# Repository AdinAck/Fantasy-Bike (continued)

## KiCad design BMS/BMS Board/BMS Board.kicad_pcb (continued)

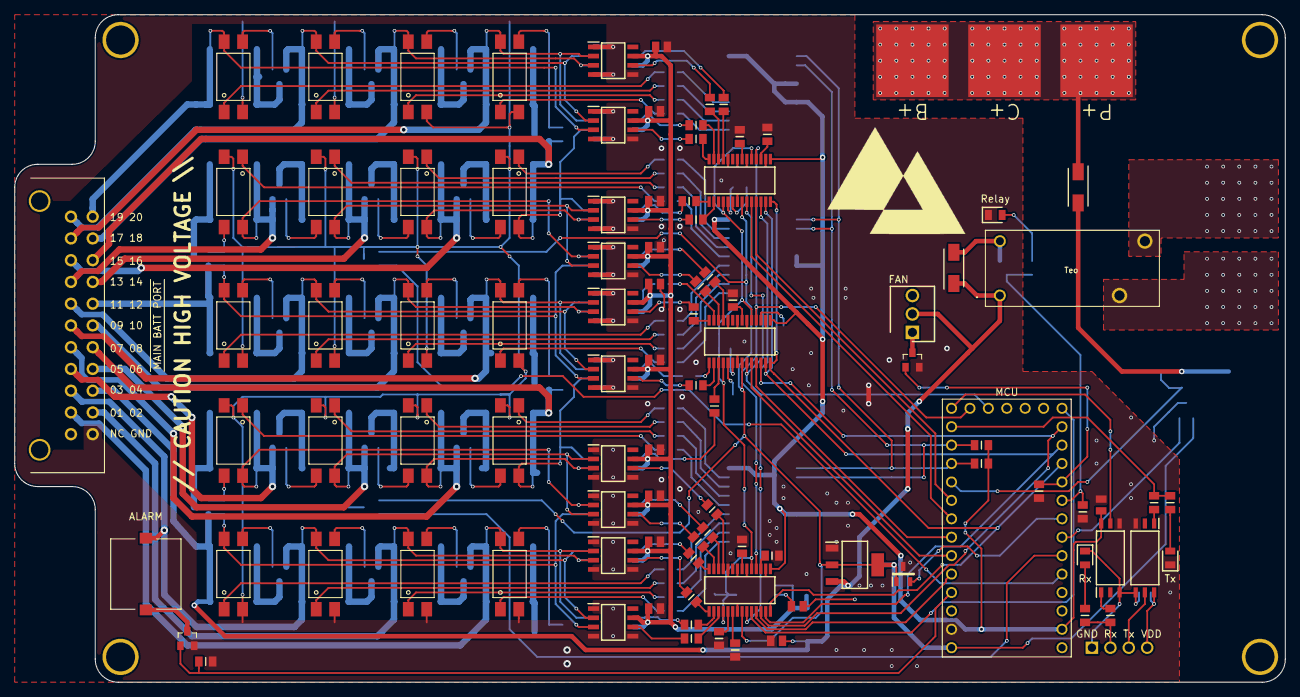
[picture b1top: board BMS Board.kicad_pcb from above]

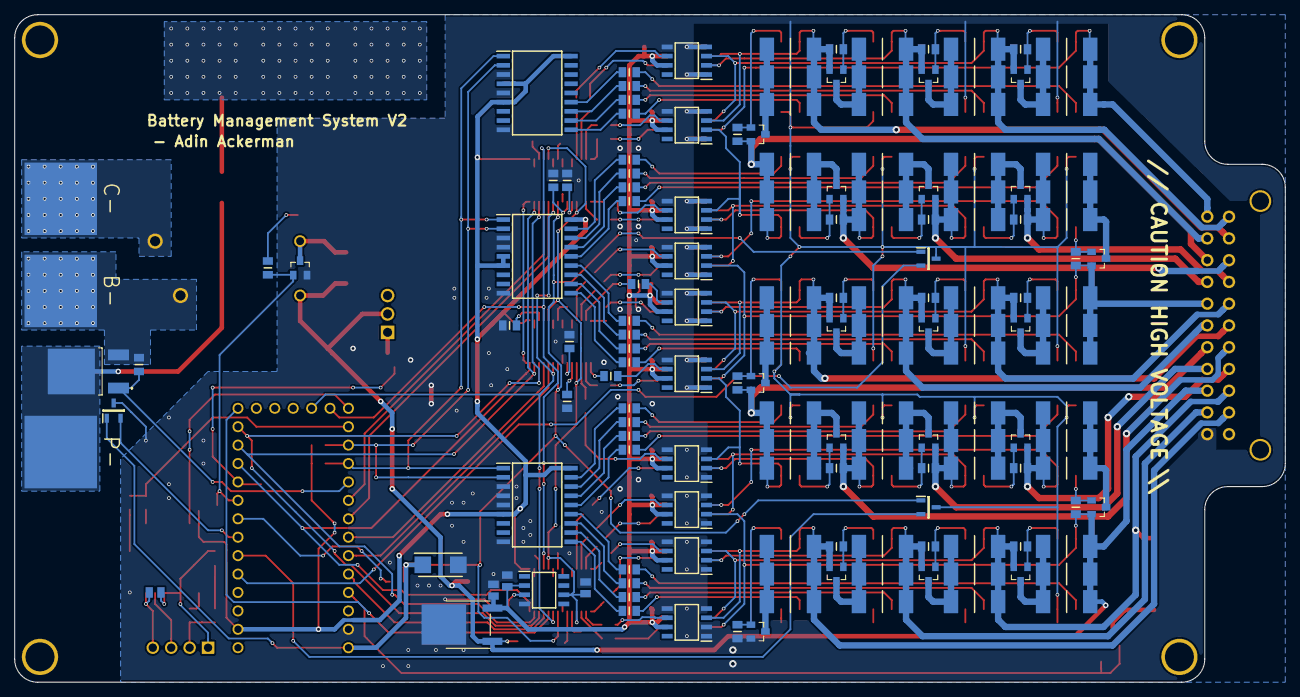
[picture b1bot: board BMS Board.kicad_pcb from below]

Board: 2 copper layers, 175.3 x 92.1 mm, 261 parts (157 on the bottom side), 197 nets.

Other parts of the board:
C18: 0805ZC104MAT2A; CAPC2012X94N
IC1, IC2: TLP2766A_TP,E; SOT127P1000X230-6N

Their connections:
/Communication/RX: IC2.5; also elsewhere on the board
unnamed 68: IC1.6; also elsewhere on the board
unnamed 69: IC1.4, IC2.3; also elsewhere on the board
unnamed 72: IC1.1; also elsewhere on the board
unnamed 74: IC1.5; also elsewhere on the board
unnamed 75: IC2.1; also elsewhere on the board

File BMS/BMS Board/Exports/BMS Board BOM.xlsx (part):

Reference | Value | Footprint | Datasheet | Capacitance | Color | Description | Height | Manufacturer_Name | Manufacturer_Part_Number | Mouser Part Number | Mouser Price/Stock | Resistance | Voltage, Current | Quantity
C1 | 08053C334KAT2A | CAPC2012X140N | https://componentsearchengine.com/Datasheets/1/08053C334KAT2A.pdf | .33 uF |  | AVX 0805 Standard 0.33uF Ceramic Multilayer Capacitor, 25 V dc, +125 | 1.4 | AVX | 08053C334KAT2A | 581-08053C334KAT2A | https://www.mouser.com/Search/Refine.aspx?Keyword=581-08053C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 |  |  | 1.0
> C2, C4-C13, C17, C18 | 0805ZC104MAT2A | CAPC2012X94N | https://componentsearchengine.com/Datasheets/1/0805ZC104MAT2A.pdf | 100nF |  | Capacitor 0805 0.1UF +/-20% 10V |  | AVX | 0805ZC104MAT2A | 581-0805ZC104MAT2A | https://www.mouser.com/Search/Refine.aspx?Keyword=581-0805ZC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 |  |  | 13.0
C3 | TPSC107K010R0150 | CAPPM6032X280N | https://componentsearchengine.com/Datasheets/1/TPSC107K010R0150.pdf | 100 uF |  | Cap Tant Solid 100uF 10V C CASE 10% (6 X 3.2 X 2.6mm) SMD 6032-28 0.15 Ohm 125C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 | 2.8 | AVX | TPSC107K010R0150 | 581-TPSC107K010R0150 | https://www.mouser.com/Search/Refine.aspx?Keyword=581-TPSC10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 |  |  | 1.0
> C14-C16 | 08053C225K4T2A | CAPC2012X94N |  | 2.2 uF |  | AVX - 08053C225K4T2A - SMD Multilayer Ceramic Capacitor, 2.2 uF, 25 V, 0805 [20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 | 0.94 | AVX | 08053C225K4T2A |  |  |  |  | 3.0
> D1, D2 | S1G | DIOM5227X250N | https://www.onsemi.com/pub/Collateral/S1M-D.pdf |  |  | ON Semi 400V 1A, Diode, 2-Pin DO-214AC S1G | 2.5 | ON Semiconductor | S1G | 512-S1G | https://www.mouser.co.uk/ProductDetail/ON-Semiconductor-Fair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 |  |  | 2.0
> H1-H4 | MountingHole | MountingHole:MountingHole_4mm_Pad_Better | ~ |  |  |  |  |  |  |  |  |  |  | 4.0
> IC1, IC2 | TLP2766A_TP,E | SOT127P1000X230-6N | https://componentsearchengine.com/Datasheets/1/TLP2766A(TP,E.pdf |  |  | High Speed Optocouplers High speed Logic output coupler; SO6L; RoHS; T&R | 2.3 | Toshiba | TLP2766A(TP,E | 757-TLP2766ATPE | https://www.mouser.co.uk/ProductDetail/Toshiba/TLP2766ATPE?q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 |  |  | 2.0
J1 | 10129379-904002BLF | HDRRA4W67P0X254_1X4_1016X254X241P | https://cdn.amphenol-icc.com/media/wysiwyg/files/drawing/101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 |  |  | Headers & Wire Housings ECONOSTIK HEADER SR RA TH 1X4 | 2.41 | Amphenol | 10129379-904002BLF | 649-1012937990402BLF | https://www.mouser.co.uk/ProductDetail/Amphenol-FCI/10129379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 |  |  | 1.0
J2 | 640456-3 | HDRV3W107P0X254_1X3_762X572X1080P | http://www.te.com/commerce/DocumentDelivery/DDEController?Ac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 |  |  | 3 way MTA straight friction lock header | 10.795 | TE Connectivity | 640456-3 | 571-6404563 | https://www.mouser.co.uk/ProductDetail/TE-Connectivity-AMP/6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 |  |  | 1.0
K1 | G5PZ-1A_DC12 | G5PZ1ADC12 | https://www.mouser.dk/datasheet/2/307/Omron_(ENG)G5PZ_E-1843616.pdf |  |  | General Purpose Relays PCB Power Relay Compact 20A, 12 VDC | 25.0 | Omron Electronics | G5PZ-1A DC12 | 653-G5PZ-1ADC12 | https://www.mouser.co.uk/ProductDetail/Omron-Electronics/G5P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 |  |  | 1.0
> LED1, LED2 | HSML-C170-T0000 | LEDC2012X90N | https://docs.broadcom.com/docs/HSML-C170-T0000-DS100 |  | Orange | CHIP,TOP MT,ALINGAP,ORG - Bulk | 0.9 | Avago Technologies | HSML-C170-T0000 | 630-HSML-C170-T0000 | https://www.mouser.co.uk/ProductDetail/Broadcom-Avago/HSML-C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 |  |  | 2.0
LED3 | HSMG-C170 | LEDC2012X80N |  |  |  | Green LED, 15 mcd 170 , 2-pin 0805 SMD Package | 0.8 | Avago Technologies | HSMG-C170 | 630-HSMG-C170 | https://www.mouser.co.uk/ProductDetail/Broadcom-Avago/HSMG-C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 |  |  | 1.0
LS1 | CMI-9705-85-SMT-TR | CMI970585SMTTR |  |  |  | Piezo Buzzers & Audio Indicators buzzer, 9.7 mm x 9.7 mm x 5 mm deep, M, 12 VDC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 | 5.5 | CUI Devices | CMI-9705-85-SMT-TR | 490-CMI-9705-85SMTTR | https://www.mouser.co.uk/ProductDetail/CUI-Devices/CMI-9705-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 |  |  | 1.0
> M1-M22 | AO3402 | Package_TO_SOT_SMD:SOT-23 | https://datasheet.lcsc.com/szlcsc/1808131821_Alpha-Omega-Sem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 |  |  |  |  |  |  |  |  |  |  | 22.0
MCU1 | ItsyBitzy_M4 | Module:Adafruit_ItsyBitsy_M4 | https://www.adafruit.com/product/3800 |  |  |  |  |  |  |  |  |  |  | 1.0
> O1-O20 | EL817(S)(C)(TU) | Package_SO:SOP-4_Optocoupler | https://www.mouser.com/datasheet/2/143/201407061833256242-36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 |  |  |  |  |  |  |  |  |  |  | 20.0
> P1-P6 | Power_Pad | SamacSys_Parts:Power_Pad |  |  |  |  |  |  |  |  |  |  |  | 6.0
PORT1 | 4.30452221E8 | Molex:430452221 |  |  |  |  |  |  |  |  |  |  |  | 1.0
PS1 | UA78M09CKVURG3 | UA78M09CKVURG3 | http://www.ti.com/lit/gpn/ua78m |  |  | 500-mA, 25-V linear voltage regulator | 2.52 | Texas Instruments | UA78M09CKVURG3 | 595-UA78M09CKVURG3 | https://www.mouser.com/Search/Refine.aspx?Keyword=595-UA78M0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 |  | 9v 500mA | 1.0
PS2 | LM1117MPX-5.0_NOPB | SOT230P700X180-4N | http://www.ti.com/lit/gpn/lm1117 |  |  | Space saving 800-mA low-dropout linear regulator with internal current limit | 1.8 | Texas Instruments | LM1117MPX-5.0/NOPB | 926-LM1117MPX5.0NOPB | https://www.mouser.com/Search/Refine.aspx?Keyword=926-LM1117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 |  | 5v 800mA | 1.0
Q1 | STD12N60DM2AG | STD13N60DM2 | https://www.st.com/resource/en/datasheet/std12n60dm2ag.pdf |  |  | Automotive-grade N-channel 600 V, 0.380 typ., 10 A MDmesh DM2 Power MOSFET in a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 | 2.0 | STMicroelectronics | STD12N60DM2AG | 511-STD12N60DM2AG | https://www.mouser.co.uk/ProductDetail/STMicroelectronics/ST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 |  |  | 1.0
Q2 | AO3402 | Package_TO_SOT_SMD:SOT-23 | https://datasheet.lcsc.com/szlcsc/1808131821_Alpha-Omega-Sem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 |  |  |  |  |  |  |  |  |  |  | 1.0
> R1-R20 | ERJ-6ENF1001V | RESC2012X70N | https://componentsearchengine.com/Datasheets/1/ERJ-6ENF1001V.pdf |  |  | Thick Film Resistors - SMD 0805 1Kohms 1% AEC-Q200 | 0.7 | Panasonic | ERJ-6ENF1001V | 667-ERJ-6ENF1001V | https://www.mouser.com/Search/Refine.aspx?Keyword=667-ERJ-6ENF1001V | 1 k |  | 20.0
> R21-R40, R101, R120-R122 | ERJ-S06F2002V | RESC2012X70N | https://www.mouser.com/datasheet/2/315/AOA0000C334-1314047.pdf |  |  | Thick Film Resistors 0805 20Kohms 1% Anti-Sulfur | 0.7 | Panasonic | ERJ-S06F2002V | 667-ERJ-S06F2002V | https://www.mouser.com/ProductDetail/Panasonic/ERJ-S06F2002V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 | 20 k |  | 24.0
> R41-R100 | CRGP2512F12R | RESC6432X65N | https://componentsearchengine.com/Datasheets/1/CRGP2512F12R.pdf |  |  | Resistor Thick Film Pulse 2512 12R 1% | 0.65 | TE Connectivity | CRGP2512F12R | 279-CRGP2512F12R | https://www.mouser.com/Search/Refine.aspx?Keyword=279-CRGP2512F12R | 12.0 |  | 60.0
> R102-R113 | ERJ-UP6J103v | RESC2012X70N | https://componentsearchengine.com/Datasheets/1/ERJ-UP6J103V.pdf |  |  | Thick Film Resistors - SMD 0805 0.5W 5% 10KOhm Anti-sulfur AEC-Q200 | 0.7 | Panasonic | ERJ-UP6J103V | 667-ERJ-UP6J103V | https://www.mouser.com/Search/Refine.aspx?Keyword=667-ERJ-UP6J103V | 10 k |  | 12.0
> R118, R119, R123-R142 | ERJ-S06J472V | RESC2012X70N | https://componentsearchengine.com/Datasheets/1/ERJ-S06J472V.pdf |  |  | Thick Film Resistors - SMD 0805 4.7Kohms 5% Anti-Sulfur | 0.7 | Panasonic | ERJ-S06J472V | 667-ERJ-S06J472V | https://www.mouser.com/Search/Refine.aspx?Keyword=667-ERJ-S06J472V | 4.7 k |  | 22.0
> R114-R117, R143 | ERJ-P06F2200V | RESC2012X70N | https://componentsearchengine.com/Datasheets/1/ERJ-P06F2200V.pdf |  |  | Thick Film Resistors - SMD 0805 220ohms 0.5W 1% AEC-Q200 | 0.7 | Panasonic | ERJ-P06F2200V | 667-ERJ-P06F2200V | https://www.mouser.com/Search/Refine.aspx?Keyword=667-ERJ-P06F2200V | 220.0 |  | 5.0
> U1-U20 | INA149AID | SOIC127P600X175-8N | http://www.ti.com/lit/ds/symlink/ina149.pdf |  |  | Texas Instruments INA149AID, Differential Amplifier 8-Pin SOIC | 1.75 | Texas Instruments | INA149AID | 595-INA149AID | https://www.mouser.com/Search/Refine.aspx?Keyword=595-INA149AID |  |  | 20.0
> U21-U24 | TMP235AEDBZTQ1 | SOT95P237X112-3N | https://www.ti.com/lit/gpn/TMP235-Q1 |  |  | Automotive +/-1.5C 2.7V to 5.5V analog output temperature sensor with -13.6 mV/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 | 1.12 | Texas Instruments | TMP235AEDBZTQ1 | 595-TMP235AEDBZTQ1 | https://www.mouser.com/Search/Refine.aspx?Keyword=595-TMP235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 |  |  | 4.0
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
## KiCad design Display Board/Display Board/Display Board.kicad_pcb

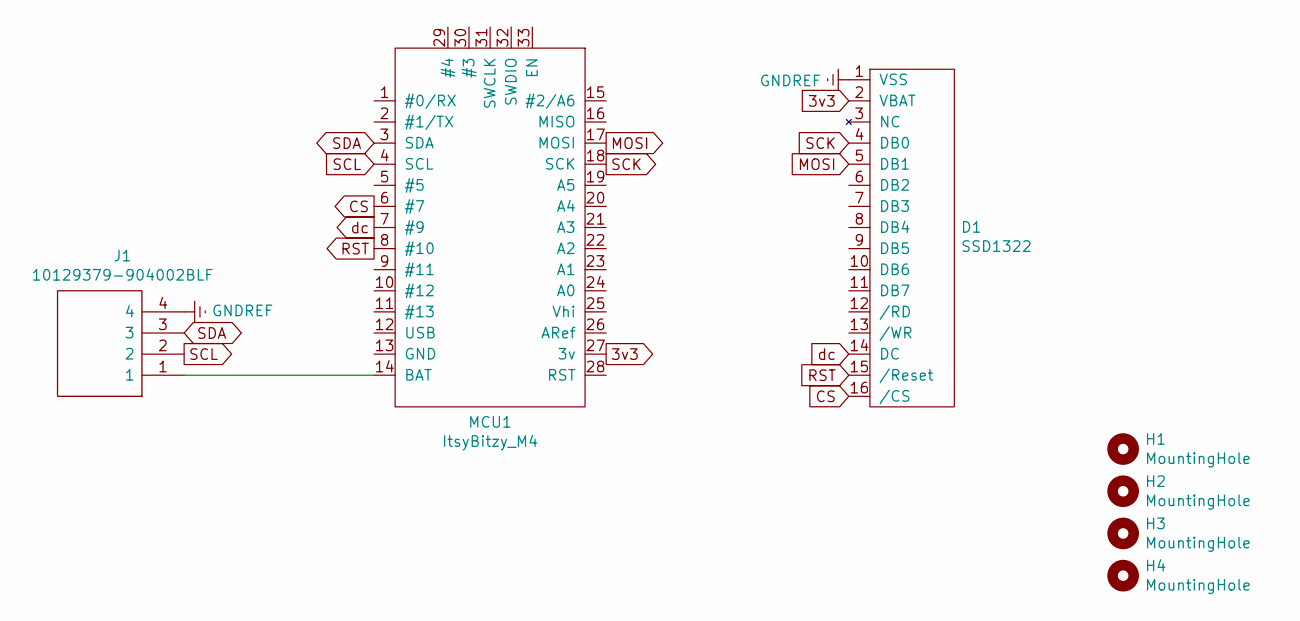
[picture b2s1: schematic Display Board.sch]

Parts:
D1: SSD1322
H1, H2, H3, H4: MountingHole; MountingHole_4mm_Pad_Better
J1: 10129379-904002BLF; HDRRA4W67P0X254_1X4_1016X254X241P; Mouser Part Number 649-1012937990402BLF
MCU1: ItsyBitzy_M4; Adafruit_ItsyBitsy_M4

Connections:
3v3: D1.2 (VBAT), MCU1.27 (3v)
CS: D1.16 (/CS), MCU1.6 (#7)
GNDREF: D1.1 (VSS), J1.4
MOSI: D1.5 (DB1), MCU1.17 (MOSI)
unnamed: J1.1, MCU1.14 (BAT)
RST: D1.15 (/Reset), MCU1.8 (#10)
SCK: D1.4 (DB0), MCU1.18 (SCK)
SCL: J1.2, MCU1.4 (SCL)
SDA: J1.3, MCU1.3 (SDA)
dc: D1.14 (DC), MCU1.7 (#9)

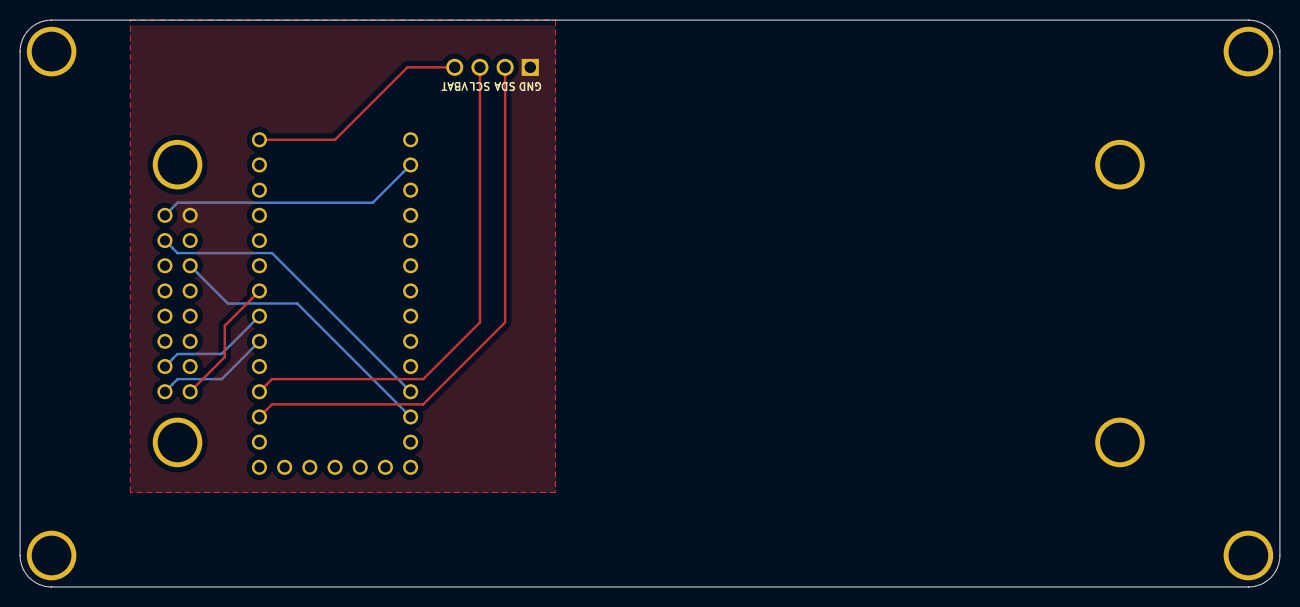
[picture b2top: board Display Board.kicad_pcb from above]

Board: 2 copper layers, 127.0 x 57.2 mm, 7 parts (1 on the bottom side), 10 nets.

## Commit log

2019-09-16 persistent variables!!!
2019-09-16 organised permvar, changed to config, now only for config file
2019-09-16 final touch ups on config
2019-09-17 improvements to config system
2019-09-17 tweeks
2019-09-17 touch ups made a config register system functionality tester
2019-10-04 got the screen going (no graphics yet) improved config register system
2019-10-04 no way register system can have nultiple instances now and will automatically seperate instances into files
2019-10-04 updated config.py to be not only config but anything, renamed RegX.py added "purge" and "test" methods(also multiple instances works)
2019-10-04 RegX: debug tool, other improvements
2019-10-05 ytuytrfy
2019-10-07 got the screen working, needed to create a function that draws a single pixel at an x,y coordinate
2019-10-09 screen is working with moving objects!!! need help on bezier curves though.
2019-10-10 Tried to make new refresh method that would write next frame before erasing old one to avoid flicker, didn't work out due to hardware restraint
2019-10-13 First commit from Ubuntu Subsystem, adding "Arduino-IDE" with "how2use.txt" inside.
2019-10-13 Created file with access token inside
2019-10-15 updated how2use.txt...
2019-10-15 just moving some things around
2019-10-15 done fixing git repo
2019-10-19 reverse bezier works with numpy root finder however it is not very good
2019-10-19 "inverse" bezier works with numpy root finder however it is not very good
2019-10-19 no longer needed files
2019-10-19 abandon ship
2019-10-20 improved RegX
2019-11-26 update...
2019-11-26 set up platformio for esp8266
2019-11-26 platformio integration
2019-11-28 alternative to bezier curve test!
2019-11-28 substitue bezier update
2020-01-09 started working on migrating display controll to sperate controller
2020-01-09 successful bytearray transfer!
2020-01-27 yay! got the display to work through itsybitsy m4!
2020-01-28 2d animation, functions for animation, and tick system
2020-01-28 adding some more shapes...
2020-02-02 ...
    ...
2020-02-05 made curve function added some test animations enabled 16 bit on u8g2 to fix screen errors
2020-02-14 animation system very operational, framerate now auto adjusts for lag
2020-02-14 added lost frame compensation
2020-02-14 documentation...
2020-02-15 sending strings works now!!!
2020-02-17 lag compensation is fully good now, importing animations from after effects!
2020-03-25 ADC communication coming along!
2020-03-26 adc reading inputs works
2020-03-26 waiting for DRDY no longer holds script
2020-03-26 ADS1248.fetchAll() works now
2020-03-26 fetchALL is gone, fetch uses range now
2020-03-26 adc.dump updates live
2020-04-02 Now multiple ADC's can be used simultaneously. More verbose.
2020-04-04 added some more things
2020-06-20 some BMS stuff, ADS1248 work, beginning work on UI library
2020-06-21 changed ui components to be classes instead of methods in Screen class
2020-06-22 adding Screen components, added "drawTriangle" to display capability
2020-06-22 cycling through screen elements with rotary encoder!
2020-06-22 "SingleDigitNumberSelector" now blinks when idle.
2020-06-22 "SingleDigitNumberSelector" can now use non-volatile memory
2020-06-22 buttons work!
2020-06-22 ...commenting
2020-06-22 test faster draw for number selector
2020-06-22 start pong
2020-06-22 rotory pong
2020-06-22 bounds errors
2020-06-22 errors fixed!
2020-06-22 ball moving, ball collision, score keeping set up
2020-06-22 score works
2020-06-22 rectangle flash, AI
2020-06-22 ai bounds, random speed
2020-06-23 AI works sometimes!
2020-06-29 renamed code.py to main.py
2020-07-03 testing ADC's on BMS!
2020-07-06 workin on BMS: using ADCs works, safety things and general BMS functions
2020-07-06 lots of more stuff added and polished
2020-07-07 mcp23008 usage is working, draining cells is set up because of this
2020-07-11 lots of stuff is changing
2020-07-26 workin on BMS also reset my computer so KiCad added some recovery files
2020-07-26 bms seems to be working!
2020-07-28 removed heat spreading algorithm due to extreme slowness
2020-07-29 BMS totally works!!!!
2020-07-30 setting up UART
